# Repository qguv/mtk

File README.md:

# mtk
_mobile/modal tool kit: a collection of useful little Arduino (Nano) programs with a menu_

I was making an Arduino rhythm game when I realized that the biggest memory hog is u8glib. Since this only needs to be imported once, loads of additional code fit fairly easily fit in memory even on the nano/micro/pro micro/etc. So it grew into a bit of an assortment of tools.

The project is designed especially to be accessable to blind/deaf users. All menus have visual and audio cues for navigation.

Blind users: Beeps of different tones can help you navigate the menus and play the game.
See the section below entited "For blind users and developers" to learn how to nagivate the menus through sound cues alone.

## Parts

  - [Arduino Nano](https://www.arduino.cc/en/Main/ArduinoBoardNano) or compatible device; if you're not using the custom shield PCB, any Arduino will work
  - headers for the above; one male set for the Nano and one female set for the shield, if you're using it
  - [128x64 I2C OLED display](http://www.hobbyelectronica.nl/product/128x64-oled-geel-blauw-i2c/)
  - a little button, normally open, closes on push; SPST/DPST/nPST-NO should be fine
  - a piezo buzzer that doesn't oscillate on its own, i.e. when you give it DC, it shouldn't make sustained noise
  - ~10kΩ resistor (anything is fine, even 1k will do, you're just pulling down, but higher impedence means less unnecessary power consumption)

## Wiring

Look at [the included Eagle files](eagle/). Here's a short explanation:

  - power (3.3v for mine) and ground the OLED display
  - attach SCL to analog pin 5 and SDA fo analog pin 4
  - make a voltage divider with 5V and the 10kΩ resistor, and make the button interrupt current from 5V to the resistor
  - connect the not-5V side of the switch to digital pin 2; this tells the board whether we're pressing the button
  - connect the (admittedly optional) buzzer to digital pin 3 and ground; add a resistor if it's too loud
  - power the board with at least 5V DC unless your board supports 3.3V

## Shield PCB

Pictured above; will add pictures of the finished product once I'm through building one. If you like the board as it is, you can [order it from OSH Park](https://oshpark.com/shared_projects/O3bcMjo5) without having to bother with EAGLE. I haven't tested it yet; I've only just ordered it myself! I don't get any money from your order; OSH Park is a simple group ordering service, and my design is open anyway.

# For blind users and developers

Here is extremely detailed information on menu sound cues and other technicalities.

## The main menu

After displaying information on time/date of compilation, the main menu will appear, allowing you to select one of many different operating modes. Tap the button to iterate through the menu. Each tap produces a "low" beep. A "high" beep is produced after you cycle past the last menu item, returning you to the first menu item. The items, in order, are:

  - Play a rhythm game
  - Measure tempo
  - Collect entropy
  - View info
  - Toggle sound

When you return to the main menu, you are placed at the title of the menu you just left. When you return from "view info", for instance, the main menu will display "view info", meaning you would tap once to select "toggle sound", twice to select "play a rhythm game", etc.

## Rhythm game gameplay

A tempo will be chosen pseudo-randomly between 60 (like a clock) and 180 (like Dutch hardstyle). The board will count eight beats at that tempo. The beeps are like a metronome: beats "1" and "5" are high, all the others are low. High low low low high low low low. You then tap out the next eight beats at the same tempo. The screen then indicates how far, in milliseconds, you ended up drifting from the tempo. It will then beep high, indicating that you can choose between either playing again at the same tempo (tap the button) or returning to the main menu (hold the button).

I'd like to expand this so that statistics are somehow given through audio. I'd also like to provide more sophisticated analysis than just 8th-beat drift.

Some specifics:

  - you can pause between the machine's 8 beats and your 8 beats--it won't count against you
  - the only thing that's (currently) measured is the first and last beats; you can rush through beats 2 through 7 and it won't count against you as long as you end up pressing beat 8 at the right time
  - the game always repeats at the same tempo until you return to the menu
  - the score is accurate to 4μs, but button pressing is not
  - the calls to `delay()` are specially designed to be very precise, on the order of 4μs or so (depending on the board), and account for screen-blit time, sound playback time, pin read/write time, calculation time, etc.

## Measuring tempo

Press the button once per beat. A current last-four-beat average will display in beats per minute on the screen. If there is more than about one second between beats, "Return?" will appear under the current tempo and a high tone will play. After this tone, you can hold to return to the main menu.

## Using the entropy generator

You can choose a base in the same way that you choose main menu items: tap to iterate and hold to select. The last item gives a higher beep than the others, indicating that you're moving to the first element again.

The bases, in order, are: 10, 16, 6, 20, 12, 64, 7. After 7 comes an option to "go back"; when the button is held here, you can return to the main menu.

Once you've held the button to select a base, the screen displays the base you chose and fills the rest of the screen with random digits in that base. Tap to generate a new screen of entropy; hold to return to the base selection screen. Note: the base selection screen always starts at 10 and does _not_ return you to your last choice, like the main menu.

The random number generator is _farily okay_. If you can ensure that analog pin zero isn't connected to any other components (PCBs notwithstanding), than the generation is the best possible without serious external hardware (a geiger counter). It uses the least significant bits of analogue reads to generate a `long int` to seed the Arduino random generation function.

  - tap to iterate through bases, hold to select and generate a screen's worth of entropy
  - you can generate another screen by simply tapping, or hold to return to base selection
  - select "Go back" after the last base to return to the main menu

## Information mode

Tap to switch screens; hold to return to the main menu. Low beep when cycling through; high beep when returning to the first element. The following information is displayed on screen at each press:

  - Made by: Quint Guvernator [github qguv/mtk](https://github.com/qguv/mtk)
  - Made at: [revspace.nl](http://revspace.nl) Hackerspace Den Haag
  - Return to: Stamkartstraat 117 2521EK Den Haag

## Turning sound on/off

Activating the fourth menu option enables or disables sound. The start-up chime will always be on. When sound is being enabled, a longer-than-normal rising chime plays. When sound is being disabled, a longer-than-normal falling chime plays.

If sound is disabled, you can re-enable it by doing the following:

  - Turn the device on
  - Tap the button four times
  - Hold the button

If this was successful, you will hear the longer-than-normal rising chime.

## Development todo

  - unify all menu code so it's easier to program menus with consistent operation and sound cues
  - unify all press-to-count cues (part two of rhythm game + tempo counter)
  - chronograph
  - count up
  - more sophisticated statistics in the rhythm game
  - a more sophisticated rhythm game
  - more modes!

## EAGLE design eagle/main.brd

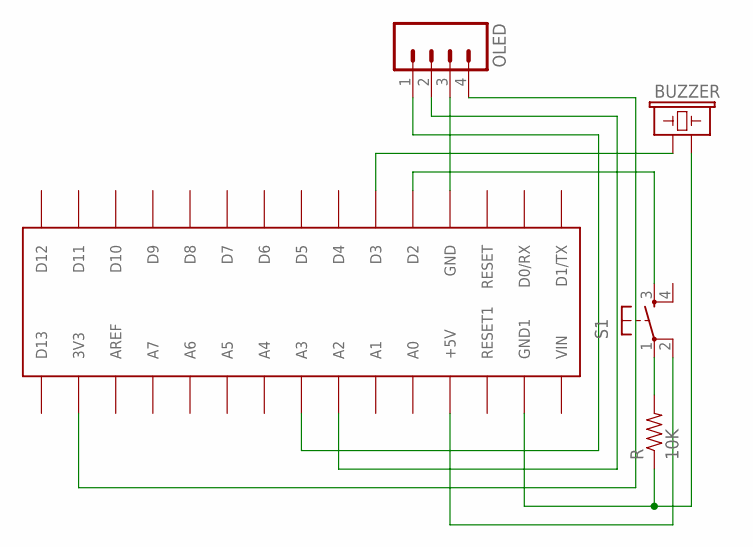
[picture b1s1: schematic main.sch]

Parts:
BUZZER: BUZZERPTH; BUZZER-12MM
NANO: ARDUINONANO; PDIP-32
OLED: M04LOCK_LONGPADS; 1X04_LOCK_LONGPADS
R: 10K; AXIAL-0.3
S1: TAC_SWITCHPTH; TACTILE-PTH

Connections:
unnamed: BUZZER.+ (1), NANO.D3
unnamed: NANO.A3, OLED.1
unnamed: NANO.A2, OLED.2
unnamed: NANO.GND, OLED.3
unnamed: R.P$2 (2), S1.1
unnamed: NANO.+5V, S1.2
unnamed: NANO.3V3, OLED.4
unnamed: NANO.D2, S1.3
unnamed: BUZZER.- (2), NANO.GND1, R.P$1 (1)

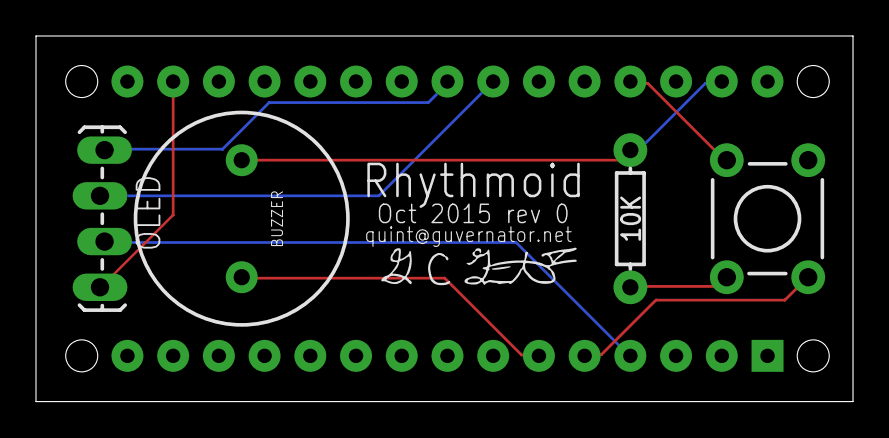
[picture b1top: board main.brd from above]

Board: 2 copper layers, 45.4 x 20.3 mm, 5 parts (1 on the bottom side), 9 nets.

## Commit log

2015-10-04 add plain-c project files
    Runs now wherever C does. Arduino C is different. Porting will mean answering
    the following quesitons:
    - How does arduino sleeping work?
    - How does Arduino wait-until-keypress work?
    - How does arduino timekeeping work?
2015-10-05 research notes for arduino port
2015-10-06 first shot at arduino port
2015-10-06 debug, pass one
2015-10-06 debug, pass two
2015-10-06 debug, pass three
2015-10-06 debug, pass four: delay fixing edition
2015-10-06 debug, pass five: stats edition
2015-10-06 debug, pass six: I hate Arduino IDE edition
2015-10-06 update todo
2015-10-06 broke u8glib
2015-10-06 add audio and visual support
2015-10-07 minor readability
2015-10-07 sound improvements
2015-10-08 add eagle schematic/board and document
2015-10-08 OSH Park link
2015-10-08 pretty picture first, wall of text second
2015-10-08 it doesn't make sense to have a posix makefile for an arduino project
2015-10-09 added entropy scaffold, but viewing doesn't work yet
2015-10-09 viewing is iffy and has obvious memory overruns, but it sorta works
2015-10-09 proper naming for better editor support
2015-10-09 better entropy collection
2015-10-09 complete entropy mode
2015-10-09 rhythm game: less instruction
2015-10-09 centered dialogues
2015-10-09 add compile information to splashscreen
2015-10-09 better sound handling
2015-10-09 fix entropy button hold bug
2015-10-09 menu uses same sound standard as other games
2015-10-09 center splash screen
2015-10-10 add information mode
2015-10-10 aesthetic improvement in rhythm game
2015-10-10 entropy: fewer bases (can easily be derived) and back option
2015-10-10 minor info text improvements
2015-10-10 minor audio feedback improvement in rhythm game
2015-10-10 entropy: base64 support
2015-10-10 better blind user support
2015-10-10 add github link to information screen
2015-10-25 I hate the Arduino IDE
2015-10-25 feature: toggle sound
2015-10-25 better chimes and blind documentation
2015-10-26 minor doc improvements
2015-10-26 much simpler button hold detection
2015-10-26 better beep sounds
2015-10-26 add tempo mode and restructure task start/finish beeps
2015-10-26 fix one beep too many in rhythm game
2015-10-26 return to home screen after inactivity on bpm
2015-10-26 add timeout option to button-hold calls
2015-10-26 style and documentation
2015-10-31 add reaction time game

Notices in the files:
parts and their libraries:
SparkFun-Electromechanical: Licensing: Creative Commons ShareAlike 4.0 International - https://creativecommons.org/licenses/by-sa/4.0
